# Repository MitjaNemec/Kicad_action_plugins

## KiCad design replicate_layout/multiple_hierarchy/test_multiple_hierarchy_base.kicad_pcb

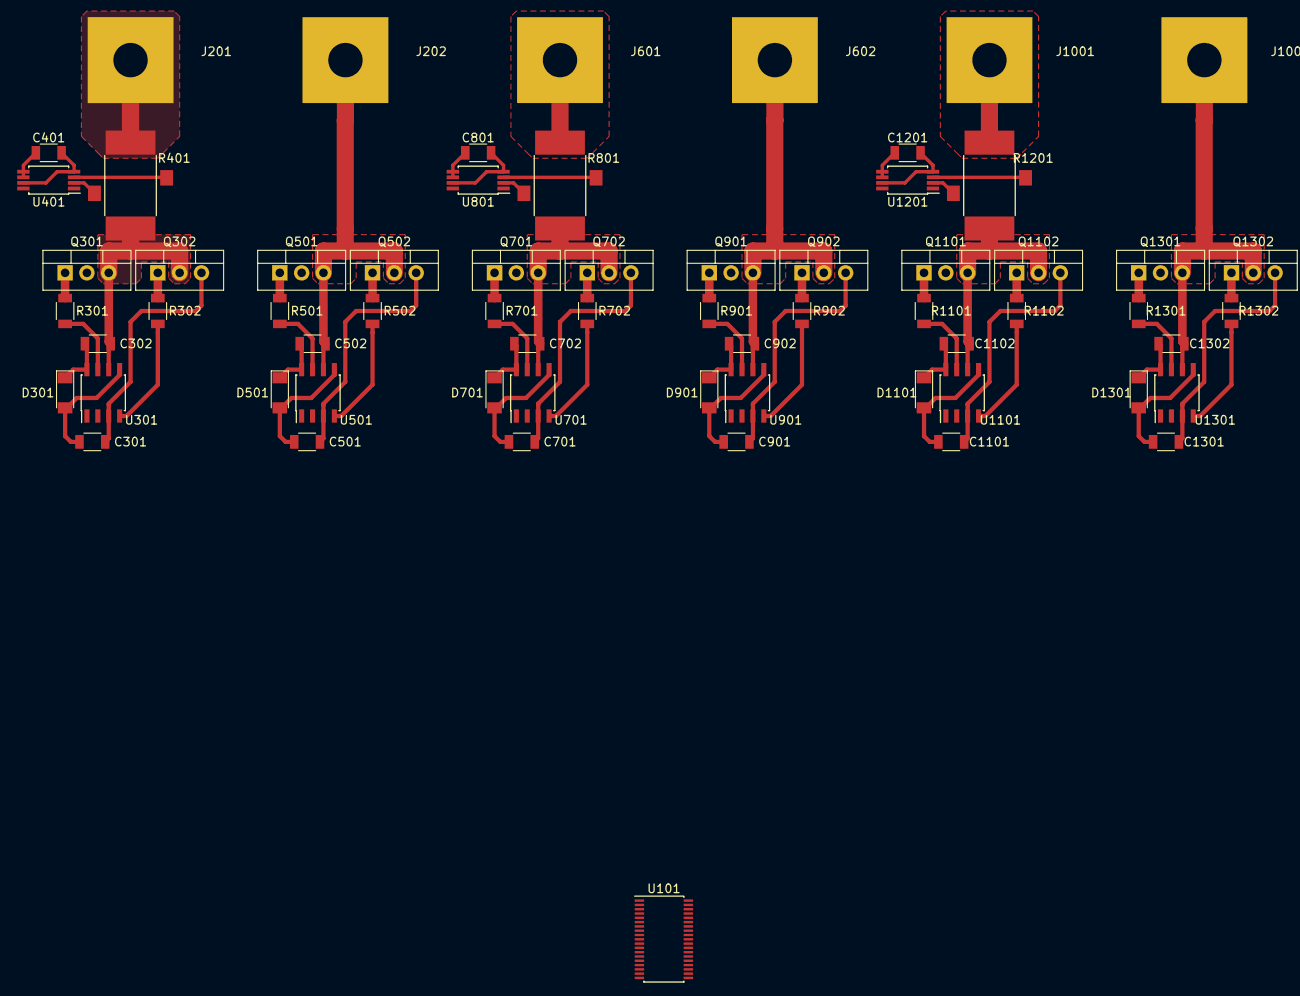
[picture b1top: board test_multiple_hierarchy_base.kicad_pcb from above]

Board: 2 copper layers, 64 parts (0 on the bottom side), 58 nets.

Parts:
C301, C302, C501, C502, C701, C702, C901, C902, C1101, C1102, C1301, C1302: 100n; C1206M
C401, C801, C1201: C1206; C1206M
D301, D501, D701, D901, D1101, D1301: LL4148; D_MiniMELF
J201, J202, J601, J602, J1001, J1002: Pusa_4mm
Q301, Q302, Q501, Q502, Q701, Q702, Q901, Q902, Q1101, Q1102, Q1301, Q1302: CSD19531KCS; TO-220
R301, R302, R501, R502, R701, R702, R901, R902, R1101, R1102, R1301, R1302: 22R; R1206M
R401, R801, R1201: R_Shunt; RM
U101: TMS320F28027DA; TSSOP-38_4.4x9.7mm_P0.5mm
U301, U501, U701, U901, U1101, U1301: IR2181; SO8
U401, U801, U1201: INA240; TSSOP-8_4.4x3mm_P0.65mm

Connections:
+3V3: C401.1, C801.1, C1201.1, U101.4, U101.22, U401.5, U401.6, U801.5, U801.6, U1201.5, U1201.6
+15V: C301.1, C501.1, C701.1, C901.1, C1101.1, C1301.1, D301.2, D501.2, D701.2, D901.2, D1101.2, D1301.2, U301.5, U501.5, U701.5, U901.5, U1101.5, U1301.5
+VDC: Q301.2, Q501.2, Q701.2, Q901.2, Q1101.2, Q1301.2
-VDC: C301.2, C401.2, C501.2, C701.2, C801.2, C901.2, C1101.2, C1201.2, C1301.2, Q302.3, Q502.3, Q702.3, Q902.3, Q1102.3, Q1302.3, U101.2, U101.12, U101.23, U301.3, U401.4, U401.7, U501.3, U701.3, U801.4, U801.7, U901.3, U1101.3, U1201.4, U1201.7, U1301.3
/Leg1/Current: U101.21, U401.8
/Leg1/Power-/OUT: C502.2, J202.1, Q501.3, Q502.2, U501.6
/Leg1/QH: U101.37, U301.1, U501.2
/Leg1/QL: U101.36, U301.2, U501.1
/Leg1/Sensor/IN: C302.2, Q301.3, Q302.2, R401.4, U301.6
/Leg1/Sensor/OUT: J201.1, R401.1
/Leg2/Current: U101.20, U801.8
/Leg2/Power-/OUT: C902.2, J602.1, Q901.3, Q902.2, U901.6
/Leg2/QH: U101.5, U701.1, U901.2
/Leg2/QL: U101.6, U701.2, U901.1
/Leg2/Sensor/IN: C702.2, Q701.3, Q702.2, R801.4, U701.6
/Leg2/Sensor/OUT: J601.1, R801.1
/Leg3/Current: U101.19, U1201.8
/Leg3/Power-/OUT: C1302.2, J1002.1, Q1301.3, Q1302.2, U1301.6
/Leg3/QH: U101.7, U1101.1, U1301.2
/Leg3/QL: U101.8, U1101.2, U1301.1
/Leg3/Sensor/IN: C1102.2, Q1101.3, Q1102.2, R1201.4, U1101.6
/Leg3/Sensor/OUT: J1001.1, R1201.1
unnamed: C302.1, D301.1, U301.8
unnamed: C502.1, D501.1, U501.8
unnamed: C702.1, D701.1, U701.8
unnamed: C902.1, D901.1, U901.8
unnamed: C1102.1, D1101.1, U1101.8
unnamed: C1302.1, D1301.1, U1301.8
unnamed: Q301.1, R301.2
unnamed: Q302.1, R302.2
unnamed: Q501.1, R501.2
unnamed: Q502.1, R502.2
unnamed: Q701.1, R701.2
unnamed: Q702.1, R702.2
unnamed: Q901.1, R901.2
unnamed: Q902.1, R902.2
unnamed: Q1101.1, R1101.2
unnamed: Q1102.1, R1102.2
unnamed: Q1301.1, R1301.2
unnamed: Q1302.1, R1302.2
unnamed: R301.1, U301.7
unnamed: R302.1, U301.4
unnamed: R401.2, U401.3
unnamed: R401.3, U401.2
unnamed: R501.1, U501.7
unnamed: R502.1, U501.4
unnamed: R701.1, U701.7
unnamed: R702.1, U701.4
unnamed: R801.2, U801.3
unnamed: R801.3, U801.2
unnamed: R901.1, U901.7
unnamed: R902.1, U901.4
unnamed: R1101.1, U1101.7
unnamed: R1102.1, U1101.4
unnamed: R1201.2, U1201.3
unnamed: R1201.3, U1201.2
unnamed: R1301.1, U1301.7
unnamed: R1302.1, U1301.4

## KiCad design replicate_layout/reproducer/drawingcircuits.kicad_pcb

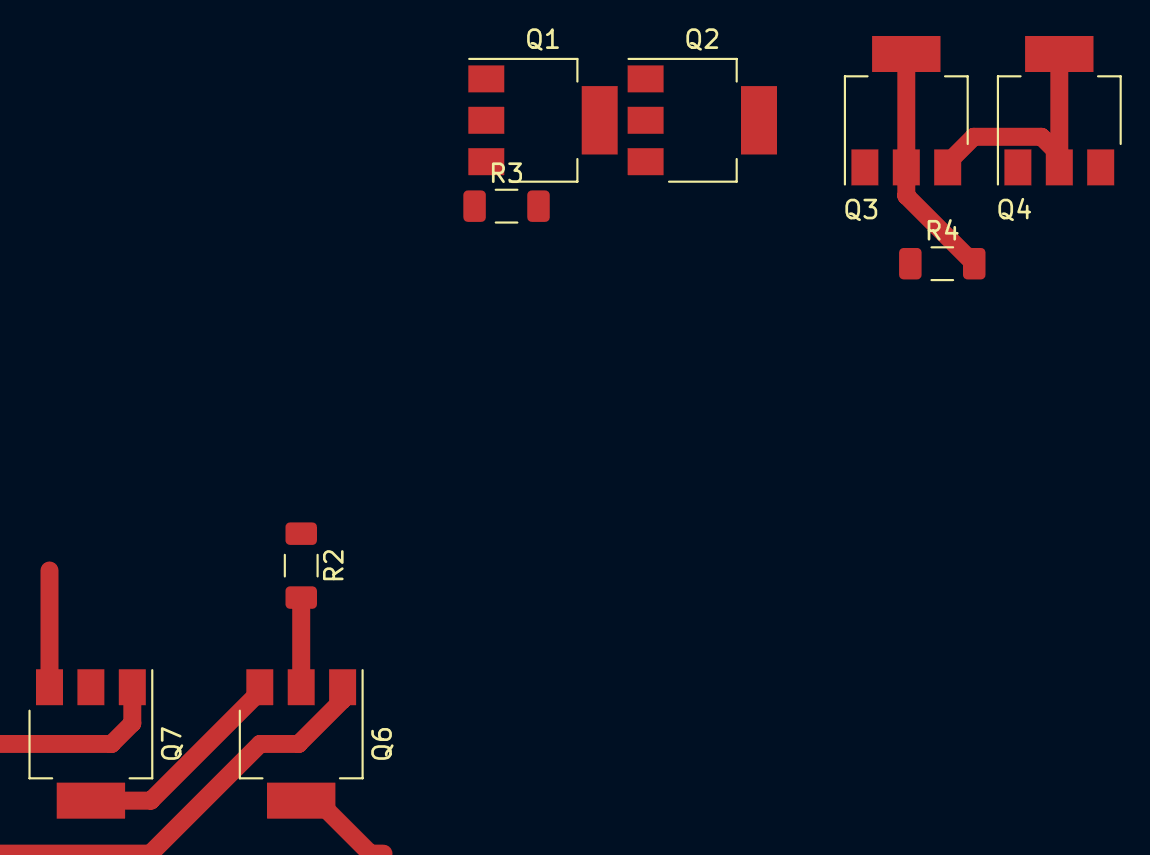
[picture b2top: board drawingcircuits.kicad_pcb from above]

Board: 2 copper layers, 9 parts (0 on the bottom side), 8 nets.

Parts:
Q1, Q2, Q3, Q4, Q6, Q7: Q_NMOS_GDS; SOT-223-3_TabPin2
R2, R3, R4: 10k; R_1206_3216Metric_2.3mmGap

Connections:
/NAND2_1/Y: Q6.2, R2.2
/SR_FLIP_FLOP_1/Q: Q2.1, Q3.2, R4.2
/SR_FLIP_FLOP_1/~Q: Q1.2, Q4.1, R3.2
GND: Q2.3, Q4.3, Q7.3
unnamed: Q1.3, Q2.2
unnamed: Q3.3, Q4.2
unnamed: Q6.3, Q7.2
VCC: R2.1, R3.1, R4.1

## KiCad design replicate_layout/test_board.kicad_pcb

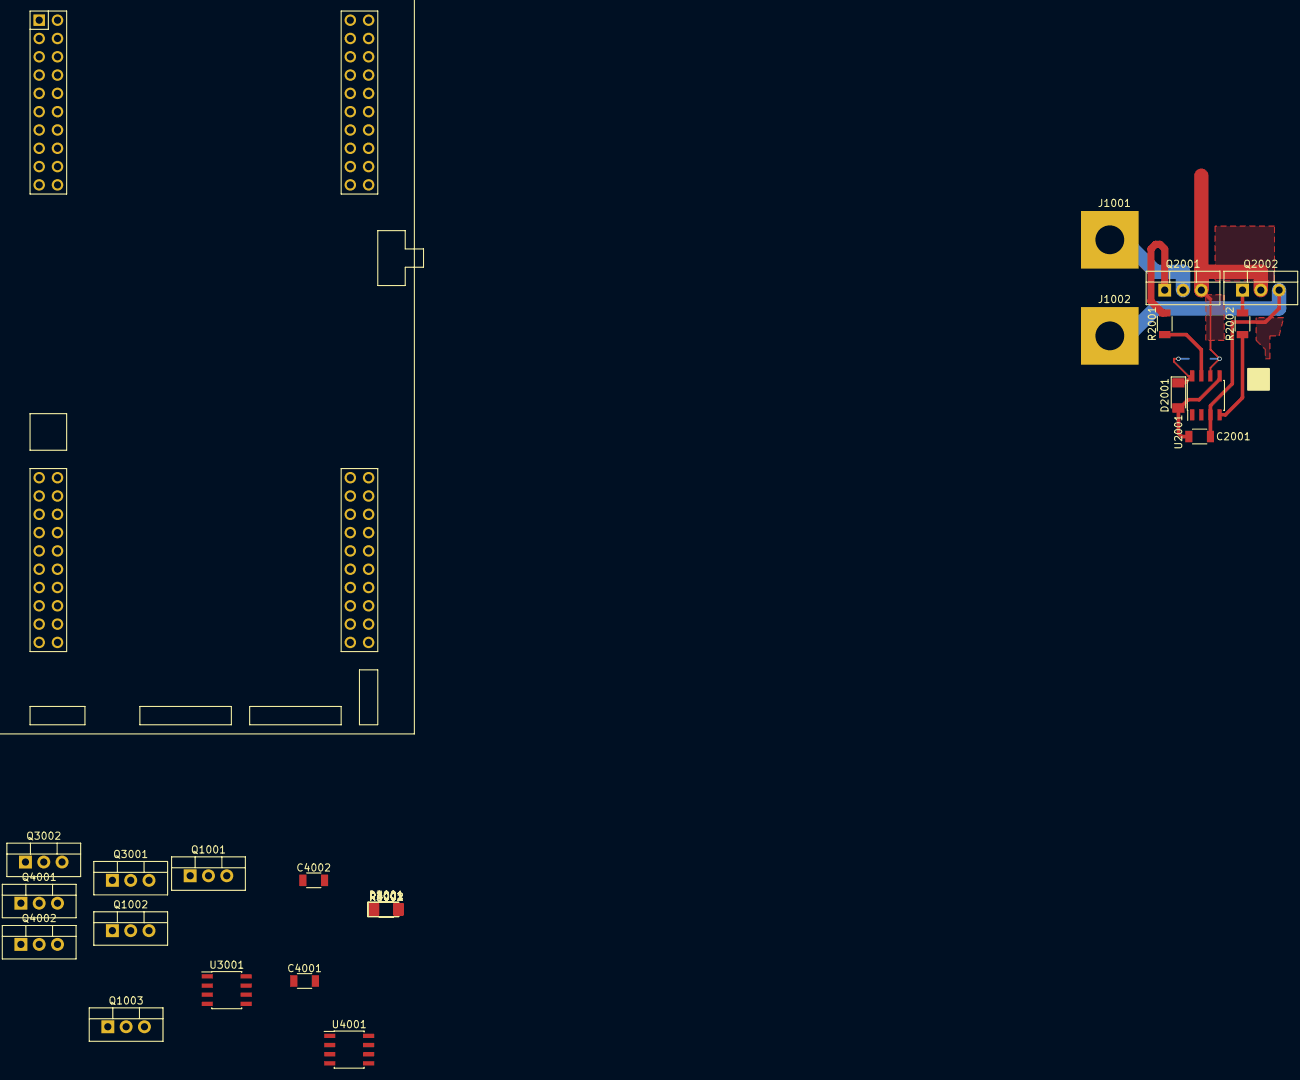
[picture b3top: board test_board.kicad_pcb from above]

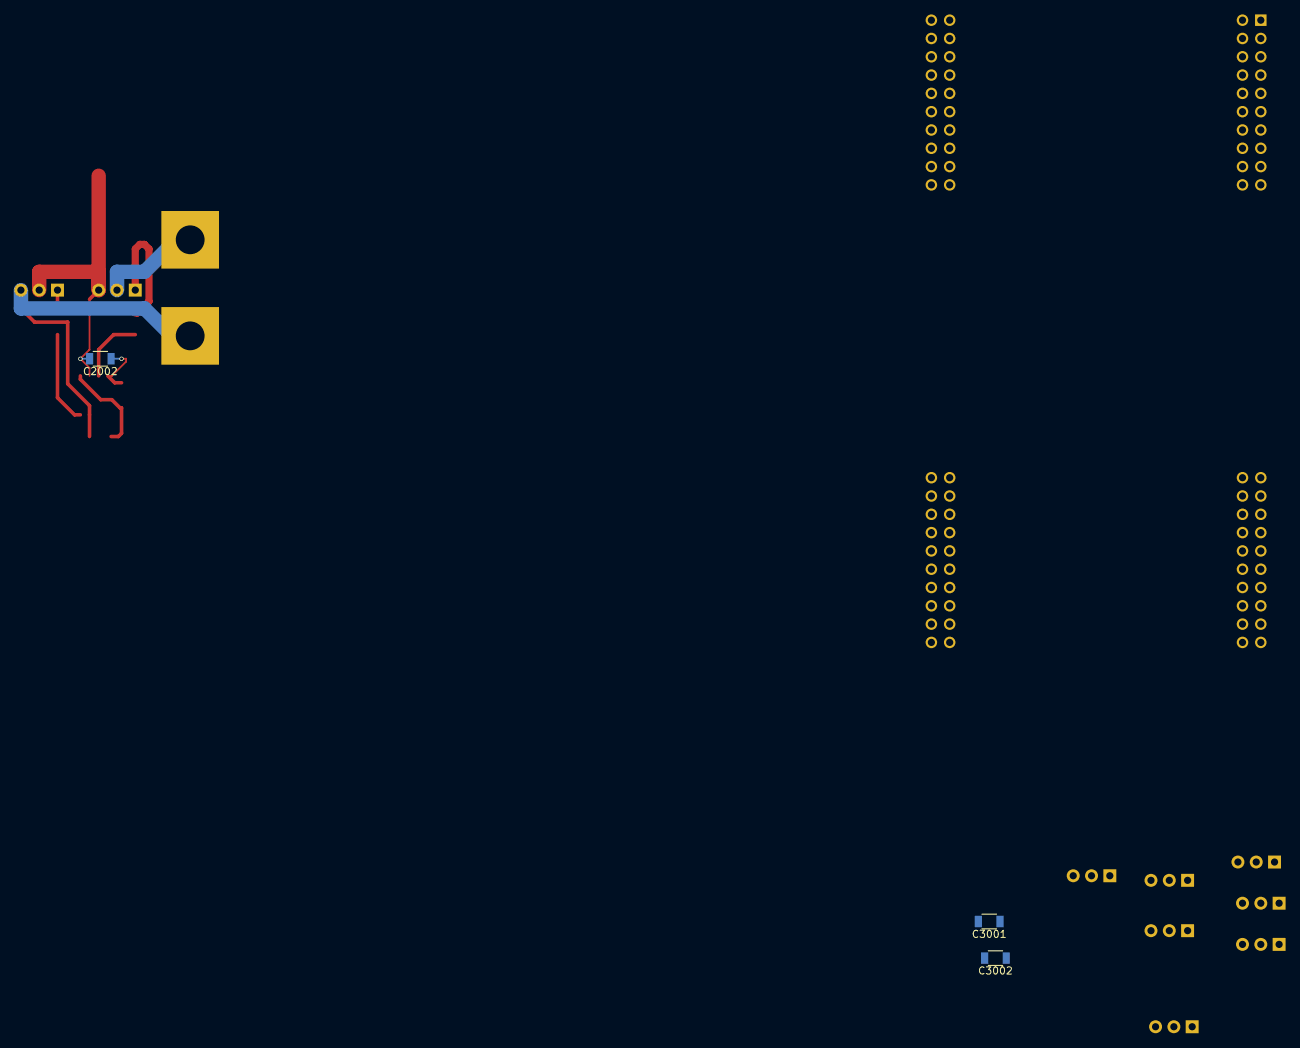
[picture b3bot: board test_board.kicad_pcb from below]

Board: 2 copper layers, 30 parts (3 on the bottom side), 27 nets.

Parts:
C2001, C2002, C3001, C3002, C4001, C4002: 100n; RC1206M
D2001, D3001, D4001: LL4148; D_MiniMELF
J1001, J1002: Pusa_4mm
Q1001, Q1002, Q1003, Q2001, Q2002, Q3001, Q3002, Q4001, Q4002: CSD19531KCS; TO-220
R2001, R2002, R3001, R3002, R4001, R4002: 20; RC1206M
U1001: LAUNCHXL-F28377S; 28379D_launchpad
U2001, U3001, U4001: IR2181; SO8

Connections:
+12V: C2001.1, C3001.1, C4001.1, D2001.2, D3001.2, D4001.2, U2001.5, U3001.5, U4001.5
+VDC: J1001.1, Q2001.2, Q3001.2, Q4001.2
/Veja_1/HIN: U1001.13, U2001.1
/Veja_1/LIN: U1001.12, U2001.2
/Veja_1/OUT: C2002.2, Q1001.1, Q2001.3, Q2002.2, U2001.6
/Veja_1/QH_G: Q2001.1, R2001.2
/Veja_1/QL_G: Q2002.1, R2002.2
/Veja_1/test/zaj: R2002.1, U2001.4
/Veja_2/HIN: U1001.35, U3001.1
/Veja_2/LIN: U1001.34, U3001.2
/Veja_2/OUT: C3002.2, Q1002.1, Q3001.3, Q3002.2, U3001.6
/Veja_2/QH_G: Q3001.1, R3001.2
/Veja_2/QL_G: Q3002.1, R3002.2
/Veja_2/test/zaj: R3002.1, U3001.4
/Veja_3/HIN: U1001.59, U4001.1
/Veja_3/LIN: U1001.56, U4001.2
/Veja_3/OUT: C4002.2, Q1003.1, Q4001.3, Q4002.2, U4001.6
/Veja_3/QH_G: Q4001.1, R4001.2
/Veja_3/QL_G: Q4002.1, R4002.2
/Veja_3/test/zaj: R4002.1, U4001.4
GND: C2001.2, C3001.2, C4001.2, J1002.1, Q2002.3, Q3002.3, Q4002.3, U2001.3, U3001.3, U4001.3
unnamed: C2002.1, D2001.1, U2001.8
unnamed: C3002.1, D3001.1, U3001.8
unnamed: C4002.1, D4001.1, U4001.8
unnamed: R2001.1, U2001.7
unnamed: R3001.1, U3001.7
unnamed: R4001.1, U4001.7
